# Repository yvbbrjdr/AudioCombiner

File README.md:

# AudioCombiner
PCB that connects your headphones and another output device to your phone.

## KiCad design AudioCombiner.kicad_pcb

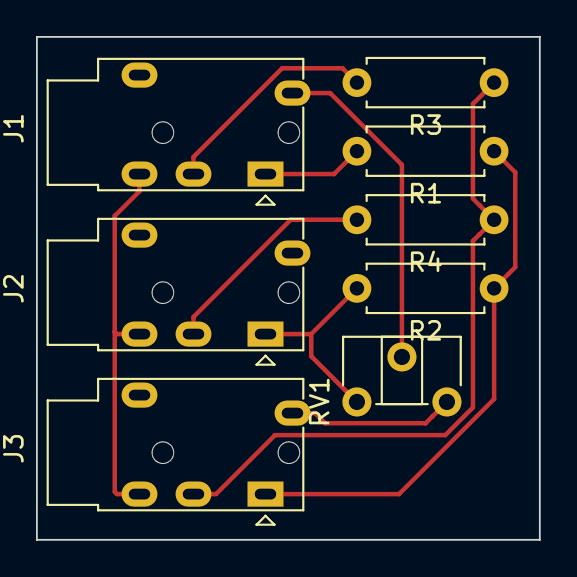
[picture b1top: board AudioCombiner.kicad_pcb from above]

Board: 2 copper layers, 27.9 x 27.9 mm, 8 parts (0 on the bottom side), 9 nets.

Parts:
J1: Primary; Jack_3.5mm_PJ320E_Horizontal
J2: Secondary; Jack_3.5mm_PJ320E_Horizontal
J3: Headphones; Jack_3.5mm_PJ320E_Horizontal
R1, R2, R3, R4: 1k; R_Axial_DIN0207_L6.3mm_D2.5mm_P7.62mm_Horizontal
RV1: Ratio; Potentiometer_ACP_CA6-H2,5_Horizontal

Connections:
unnamed: J1.R1, R3.2
unnamed: J1.R2, J2.R2, J3.R2
unnamed: J1.S, RV1.2
unnamed: J1.T, R1.2
unnamed: J2.R1, R4.2
unnamed: J2.T, R2.2, RV1.1
unnamed: J3.R1, R3.1, R4.1
unnamed: J3.S, RV1.3
unnamed: J3.T, R1.1, R2.1

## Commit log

2019-12-26 THT audio jack
